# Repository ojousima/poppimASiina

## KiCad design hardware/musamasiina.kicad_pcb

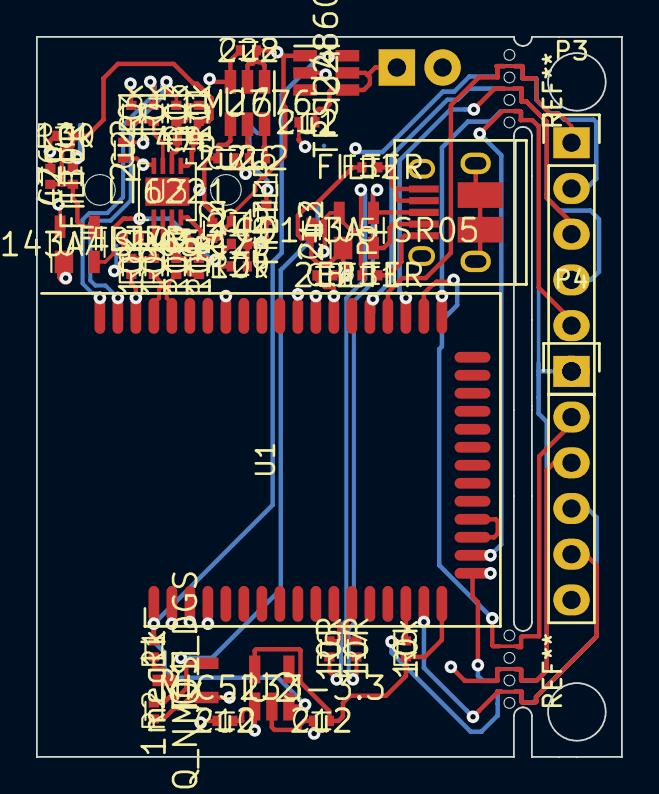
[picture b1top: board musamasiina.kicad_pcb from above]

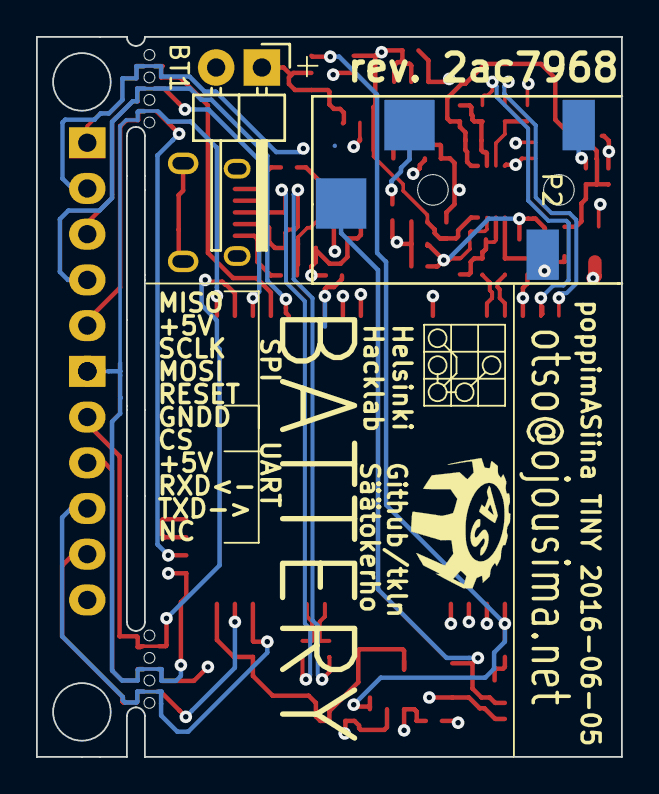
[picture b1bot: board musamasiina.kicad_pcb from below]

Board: 4 copper layers, 32.5 x 40.0 mm, 48 parts (2 on the bottom side), 39 nets.

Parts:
BT1: Battery; Pin_Header_Angled_1x02
C1, C2, C3, C6, C7, C8, C10, C11, C12, C13, C28: 2u2; SMD0402-CAP-N
C4, C5, C26, C27: 47p; SMD0402-CAP-N
FB1, FB2, FB9, FB10, FB11: FILTER; SMD0402-FERRITE-N
P1: USB_OTG; USB_Micro-B_10103594-0001LF
P2: CONN_01X04; SMD_3-5mm_jack_CUI-SJ-352X-SMT
P3: CONN_02X03; Pin_Header_Straight_1x06
P4: CONN_01X06; Pin_Header_Straight_1x06
Q1: Q_NMOS_DGS; SOT23-M
R1: 1k; SMD0402-RES-N
R2: 1meg; SMD0402-RES-N
R3, R4, R5, R8, R9, R10, R11, R12, R13, R29, R30: 10k; SMD0402-RES-N
R6, R7: 10R; SMD0402-RES-N
U1: WT32
U2: MIC5233-3.3; SOT23-5-M
U3: LT6221; DFN-8-EP-0_5mm_3x3mm-N
U4: TPS22860; SOT23-6-M
U5, U7: CD143A-SR05; SOT143-N
U6: LM2776; SOT23-6-M

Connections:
+5V: C13.1, FB1.2, P3.2, P4.3, U1.38, U5.4
+BATT: BT1.1, C8.1, C10.1, C11.1, Q1.1, R2.1, U1.37, U2.1, U4.4, U4.5
/AUDIO_SWITCH: P2.4, Q1.2, R2.2
/CD+: R7.1, U1.12
/CD-: R6.1, U1.11
/CS: P4.2, U1.32
/LO_N: R13.2, U1.49
/LO_P: R4.2, U1.50
/MISO: P3.1, U1.34
/MOSI: P3.4, U1.35
/Power Supply/ENABLE: R1.1, U1.1, U2.3, U4.6
/Power Supply/GNDBUS: FB2.1, P1.4, P1.5
/Power Supply/VBUS: FB1.1, P1.1
/RESET: P3.5, U1.19
/RO_N: R10.2, U1.46
/RO_P: R9.2, U1.47
/RXD: P4.4, R5.1, U1.15
/SCLK: P3.3, U1.33
/Stereo out/GROUND_CABLE: FB11.2, P2.2
/Stereo out/LEFT_CABLE: FB9.2, P2.1
/Stereo out/LEFT_DEVICE: C4.1, C26.1, FB9.1, R11.1, R30.1, U3.1, U7.3
/Stereo out/RIGHT_CABLE: FB10.2, P2.3
/Stereo out/RIGHT_DEVICE: C5.1, C27.1, FB10.1, R12.1, R29.1, U3.7, U7.2
/TXD: P4.5, U1.16
/USB_D+: P1.3, R7.2, U5.3
/USB_D-: P1.2, R6.2, U5.2
GNDA: C1.2, C2.2, C7.2, C26.2, C27.2, C28.2, FB11.1, R3.2, R8.2, R29.2, R30.2, U1.39, U1.43, U1.48, U4.2, U6.3
GNDD: BT1.2, C8.2, C10.2, C11.2, C12.2, C13.2, FB2.2, P3.6, P4.1, U1.2, U1.3, U1.4, U1.18, U1.31, U2.2, U5.1
unnamed: C4.2, R11.2, R13.1, U3.2
unnamed: C5.2, R10.1, R12.2, U3.6
unnamed: C6.1, U6.5
unnamed: C6.2, U6.6
unnamed: Q1.3, R1.2
unnamed: R3.1, R4.1, U3.3
unnamed: R8.1, R9.1, U3.5
unnamed: U1.20, U1.21
VAA: C1.1, C3.1, C28.1, U3.8, U4.1, U6.1, U6.2, U7.4
VDD: C12.1, R5.2, U1.17, U2.5
VEE: C2.1, C3.2, C7.1, U3.4, U6.4, U7.1

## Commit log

2016-05-15 add wt32 library symbol
2016-05-15 Ignore kicad backup, autogenerated files
2016-05-15 Setup libraries
2016-05-15 Add header, printout
2016-05-15 Add simulation model
2016-05-15 Ignore LTSpice raw data
2016-05-15 Add printouts of simulation results
2016-05-15 Add analog sections to schematic
2016-05-15 Update schematic printout
2016-05-15 Fix ESD-protection diodes
2016-05-15 Update printouts
2016-05-15 Start vorking on PSU
2016-05-15 Update printout
2016-05-19 Schematic ready for review
2016-05-19 Update header, printout
2016-05-19 Rename *.sch.svg into *.svg
2016-05-20 Fix #2
    Corrected BAT54S pin order, updated schematic
2016-05-20 Add AC-coupling caps to mic input. Fixes #4
2016-05-21 divide schematic into subscheets
2016-05-21 Add user IO, programming headers
2016-05-21 update schematic headers, printouts
2016-05-21 Revert "Rename *.sch.svg into *.svg"
    This reverts commit bb40c55cd4a211b7ce9199351595c3e4f8af534e.
2016-05-21 Include tps22860 library symbol in project
2016-05-21 Add standard footprints
2016-05-21 Fix annotation of VESD resistors
2016-05-21 draft PCB outline, import standard components
2016-05-23 Start placement of parts
2016-05-24 Update footprints
2016-05-24 Continue placing parts
2016-05-28 Add resistors from audio IO to gnd, fixes #10
2016-05-28 Fix #9
2016-05-28 Fix #8
2016-05-28 Adjust layout
2016-05-28 Add KiCAD footprints to project folder
2016-05-31 Update schematics
2016-05-31 Add WT32 3D model
2016-05-31 Update layout
2016-05-31 Add music sample to simulation
2016-05-31 Fix annotation of VESD resistors
    Fix annotation of VESD resistors
2016-06-04 Make minimal circuitry
2016-06-04 Layout board
2016-06-04 Add production files, printouts
2016-06-10 Finalize design
2016-06-18 Add isl21080 library symbol
